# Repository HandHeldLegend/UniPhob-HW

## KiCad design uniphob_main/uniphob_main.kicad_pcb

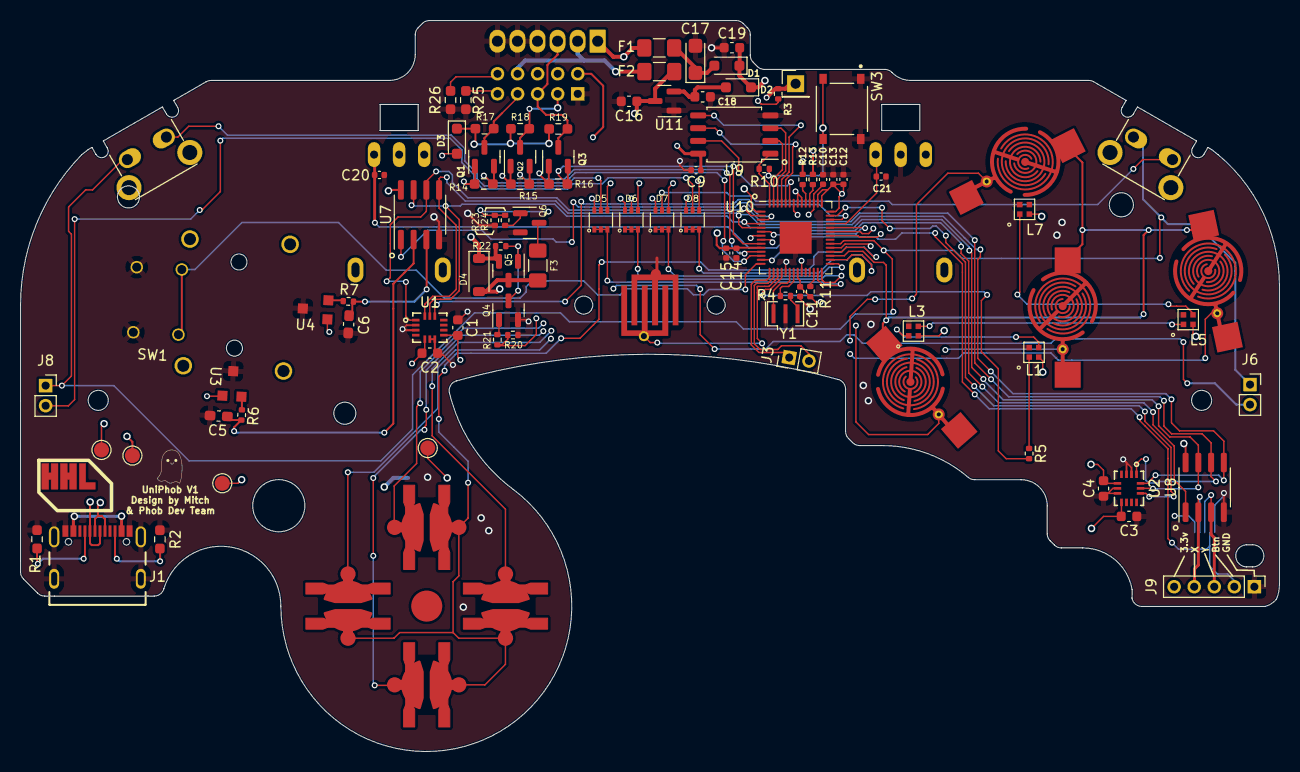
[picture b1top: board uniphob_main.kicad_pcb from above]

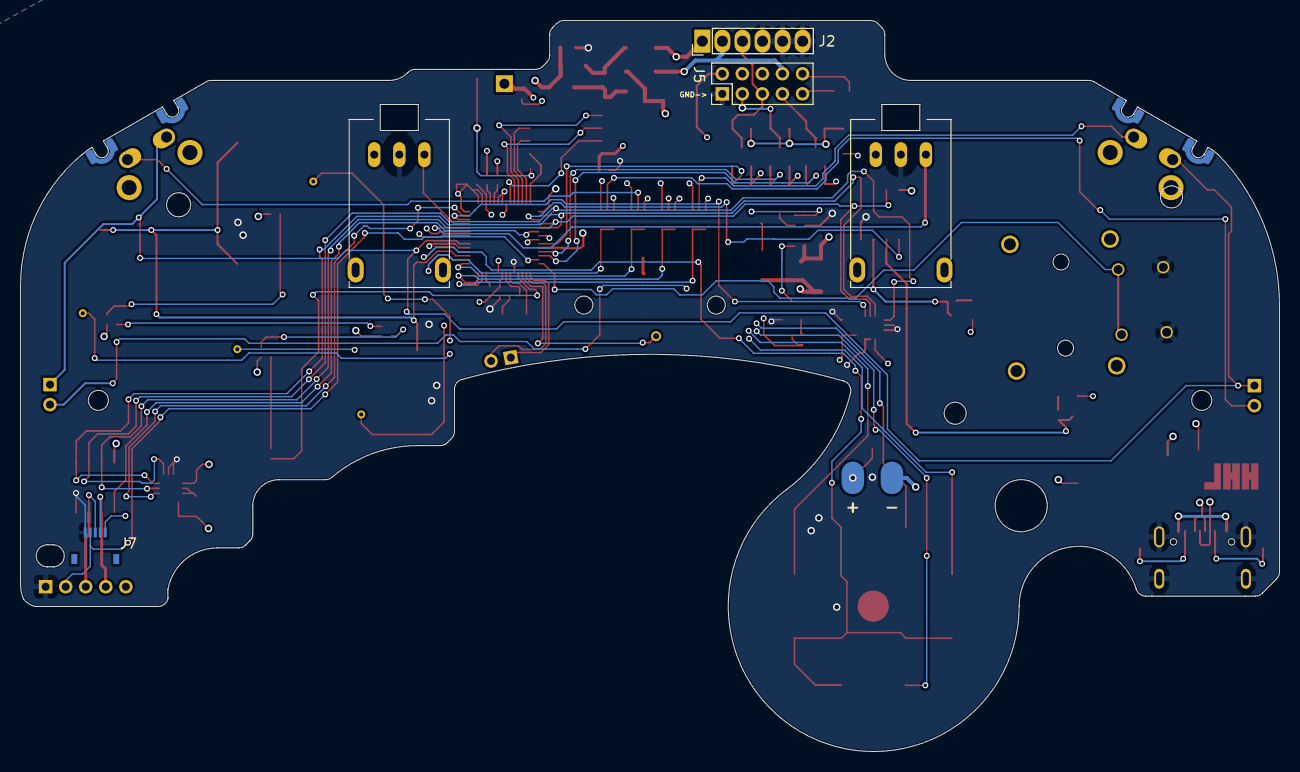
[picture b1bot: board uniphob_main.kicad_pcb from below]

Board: 4 copper layers, 125.5 x 72.9 mm, 103 parts (6 on the bottom side), 87 nets.

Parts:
C1, C2, C3, C4: 100nF; C_0603_1608Metric
C5, C6: .047u; C_0603_1608Metric_Pad1.08x0.95mm_HandSolder
C9, C10, C11, C12, C14, C15, C20, C21: 100n; C_0402_1005Metric
C13: 1u; C_0402_1005Metric
C16, C18: 2.2uF; C_0603_1608Metric
C17: 47uF 6.3v; CP_EIA-3216-18_Kemet-A
C19: 10u; C_0603_1608Metric
D1, D2, D3: CUS08F30; D_SOD-323_HandSoldering
D4: M7C; D_SOD-123
D5, D6, D7, D8: BAS16VY,115; SOT-363_SC-70-6
F1, F2, F3: Fuse; Fuse_1206_3216Metric_Pad1.42x1.75mm_HandSolder
J1: USB4105-GF-A-060; GCT_USB4105-GF-A-060
J2: Conn_01x06_Female; GCC_Header_Straight_1x06_Pitch2.00mm
J3: Conn_01x02_Pin; PinHeader_1x02_P2.00mm_Vertical
J4: Rumble; rumble_pins
J5: Conn_02x04_Counter_Clockwise; PinSocket_2x05_P2.00mm_Vertical
J6, J8: Conn_01x02_Socket; PinSocket_1x02_P2.00mm_Vertical
J7: Conn_01x05_Pin; molex_5034800540
J9: Conn_01x05_Pin; PinHeader_1x05_P2.00mm_Vertical
L1, L3, L5, L7: SK6805-EC-15
P1: Endpoint; PinHeader_1x01_P2.54mm_Vertical
Q1, Q2, Q3: BSS138; SOT-23
Q4, Q6: Q_NMOS_GSD; SOT-23
Q5: Q_PMOS_GDS; SOT-23
R1, R2, R25, R26: 5.1k; R_0603_1608Metric_Pad0.98x0.95mm_HandSolder
R3: 500K; R_0402_1005Metric
R4, R6, R7, R10: 1k; R_0402_1005Metric
R5: 330; R_0402_1005Metric
R11, R20, R22, R23: 10k; R_0402_1005Metric
R12, R13: 27; R_0402_1005Metric
R14, R15, R16, R17, R18, R19: 1k; R_0603_1608Metric_Pad0.98x0.95mm_HandSolder
R21, R24: 100R; R_0402_1005Metric
RV1, RV2: Slider_GCC-Gamecube_MB; GCC_Slider
SW1: GL18_SW; GL18
SW3: TS-1187A-B-A-B; SW_TS-1187A-B-A-B
SW4, SW5, SW6, SW7: BPAD; ABXY_Contact_Omron_Switch_Circley
SW8, SW9, SW10, SW11: DPAD; Dpad_Contact_TL3315NF_2_gba
SW12, SW14: BPAD; Z_Switch_Edge_Omron
SW16: BPAD; Start_Contact
TP1, TP2, TP5, TP7: TestPoint; TestPoint_Pad_D1.5mm
U1, U2: ST_LSM6; LGA14
U3, U4: GH39F (Hall SOT23); GH39F
U7, U8: MCP3002; SOIC-8_3.9x4.9mm_P1.27mm
U9: W25Q128JVS; SOIC-8_5.23x5.23mm_P1.27mm
U10: RP2040; QFN-56-1EP_7x7mm_P0.4mm_EP3.2x3.2mm
U11: LP3986-33B3F; SOT-23
Y1: Crystal_GND3; Resonator_SMD_Murata_CSTxExxV-3Pin_3.0x1.1mm

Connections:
+1V1: C10.2, U10.23 (DVDD), U10.45 (VREG_VOUT), U10.50 (DVDD)
+3.3V_PRE: F1.1, J2.1, J5.8
+3V3: C1.2, C2.2, C3.2, C4.2, C9.1, C11.1, C12.1, C13.1, C14.2, C15.2, C19.2, D1.1 (K), D2.1 (K), D3.2 (A), J7.5, J9.5, L1.2 (VDD), L3.2 (VDD), L5.2 (VDD), L7.2 (VDD), Q1.1 (G), Q2.1 (G), Q3.1 (G), R11.1, R14.1, R15.1, R16.1, RV1.1 (V+), RV2.1 (V+), TP7.1, U1.5 (VDDIO), U1.8 (VDD), U2.5 (VDDIO), U2.8 (VDD), U3.1 (VDD), U4.1 (VDD), U7.8 (VDD/VREF), U8.8 (VDD/VREF), U9.8 (VCC), U10.1 (IOVDD), U10.10 (IOVDD), U10.22 (IOVDD), U10.33 (IOVDD), U10.42 (IOVDD), U10.43 (ADC_AVDD), U10.44 (VREG_IN), U10.48 (USB_VDD), U10.49 (IOVDD)
+5V: C16.1, D4.1 (K), F2.2, J4.1, Q5.2 (S), R22.2, TP5.1, U11.3 (VI)
+5V_PRE: F2.1, J1.A4_B9 (VBUS), J1.B4_A9 (VBUS), J2.2, J5.7
/QSPI_SCLK: U9.6 (CLK), U10.52 (QSPI_SCLK)
/QSPI_SD0: U9.5 (DI(IO0)), U10.53 (QSPI_SD0)
/QSPI_SD1: U9.2 (DO(IO1)), U10.55 (QSPI_SD1)
/QSPI_SD2: U9.3 (IO2), U10.54 (QSPI_SD2)
/QSPI_SD3: U9.7 (IO3), U10.51 (QSPI_SD3)
/QSPI_SS: R10.1, U9.1 (~CS), U10.56 (QSPI_SS)
/RUN: R11.2, U10.26 (RUN)
/~USB_BOOT: R10.2, SW3.C, SW3.D
ABXY_RGB: L1.1 (DIN), R5.1
A_Pull: D7.6 (K), SW4.2
B_Pull: D8.6 (K), SW5.2
CC1: J5.5, R25.1
CC2: J5.6, R26.2
D+: J1.A6 (DP1), J1.B6 (DP2), J5.10, R12.1, TP2.1
D-: J1.A7 (DN1), J1.B7 (DN2), J5.9, R13.1, TP1.1
DD_Pull: D6.4 (K), SW9.2
DL_Pull: D8.4 (K), SW10.2
DR_Pull: D7.4 (K), SW11.2
DU_Pull: D5.4 (K), SW8.2
GND: C1.1, C2.1, C3.1, C4.1, C5.1, C6.1, C9.2, C10.1, C11.2, C12.2, C13.2, C14.1, C15.1, C16.2, C17.2, C18.2, C19.1, C20.2, C21.2, J1.A1_B12 (GND), J1.B1_A12 (GND), J1.S1 (SHELL_GND), J1.S2 (SHELL_GND), J1.S3 (SHELL_GND), J1.S4 (SHELL_GND), J2.4, J2.5, J2.6, J5.1, J7.1, J9.1, L1.4 (GND), L3.4 (GND), L5.4 (GND), L7.4 (GND), Q4.2 (S), Q6.2 (S), R1.2, R2.2, R20.1, R23.1, R25.2, R26.1, RV1.2 (GND), RV2.2 (GND), SW1.S3 (3), SW1.S4 (4), SW3.A, SW3.B, SW16.1, U1.2 (SDx), U1.3 (SCx), U1.6 (GNDIO), U1.7 (GND), U2.2 (SDx), U2.3 (SCx), U2.6 (GNDIO), U2.7 (GND), U3.3 (GND), U4.3 (GND), U7.4 (VSS), U8.4 (VSS), U9.4 (GND), U10.19 (TESTEN), U10.57 (GND), U11.1 (GND), Y1.2
IMU0_CS: U1.12 (CS), U10.40 (GPIO28_ADC2)
IMU1_CS: U2.12 (CS), U10.41 (GPIO29_ADC3)
LADC_CS: U7.1 (~CS/SHDN), U10.3 (GPIO1)
LS_BUTTON: SW1.S1 (1), SW1.S2 (2), U10.14 (GPIO11)
LX: C5.2, R6.2, U7.2 (CH0)
LY: C6.2, R7.2, U7.3 (CH1)
L_ANALOG: C20.1, RV1.3 (Signal), U10.38 (GPIO26_ADC0)
L_Pull: D8.5 (K), J8.2
N_CLOCK: J5.2, Q2.3 (D), R18.2
N_CLOCK_3.3: Q2.2 (S), R15.2, U10.11 (GPIO8)
N_DATA: J2.3, J5.3, Q3.3 (D), R19.2
N_DATA_3.3: Q3.2 (S), R16.2, U10.9 (GPIO7)
N_LATCH: J5.4, Q1.3 (D), R17.2
N_LATCH_3.3: Q1.2 (S), R14.2, U10.12 (GPIO9)
unnamed: C17.1, D1.2 (A), F1.2
unnamed: C18.1, D2.2 (A), U11.2 (VO)
unnamed: J1.A5 (CC1), R1.1
unnamed: J1.B5 (CC2), R2.1
unnamed: L1.3 (DOUT), L3.1 (DIN)
unnamed: L3.3 (DOUT), L5.1 (DIN)
unnamed: L5.3 (DOUT), L7.1 (DIN)
unnamed: Q4.3 (D), Q5.1 (G), R22.1
unnamed: Q4.1 (G), R21.2
unnamed: F3.2, Q6.3 (D)
unnamed: Q6.1 (G), R24.2
unnamed: R4.1, Y1.3
unnamed: R6.1, U3.2 (VOUT)
unnamed: R7.1, U4.2 (VOUT)
unnamed: R13.2, U10.46 (USB_DM)
unnamed: R12.2, U10.47 (USB_DP)
Push_A: D5.1 (A), D5.2 (A), D5.3 (A), U10.27 (GPIO16)
Push_B: D6.1 (A), D6.2 (A), D6.3 (A), U10.28 (GPIO17)
Push_C: D7.1 (A), D7.2 (A), D7.3 (A), U10.29 (GPIO18)
Push_D: D8.1 (A), D8.2 (A), D8.3 (A), U10.30 (GPIO19)
RADC_CS: U8.1 (~CS/SHDN), U10.6 (GPIO4)
RGB_OUT: R5.2, U10.18 (GPIO15)
RS_BUTTON: J7.2, J9.2, U10.13 (GPIO10)
RUMBLE: R23.2, R24.1, U10.37 (GPIO25)
RUMBLE-: D4.2 (A), F3.1, J4.2, Q5.3 (D)
RX: J7.4, J9.4, U8.2 (CH0)
RY: J7.3, J9.3, U8.3 (CH1)
R_ANALOG: C21.1, RV2.3 (Signal), U10.39 (GPIO27_ADC1)
R_BRAKE: R20.2, R21.1, U10.36 (GPIO24)
R_Pull: D6.5 (K), J6.2
SHARED_PU: D3.1 (K), R17.1, R18.1, R19.1
SPI_CK: U1.13 (SCL), U2.13 (SCL), U7.7 (CLK), U8.7 (CLK), U10.4 (GPIO2)
SPI_RX: U1.1 (SDO), U2.1 (SDO), U7.6 (DOUT), U8.6 (DOUT), U10.2 (GPIO0)
SPI_TX: U1.14 (SDA), U2.14 (SDA), U7.5 (DIN), U8.5 (DIN), U10.5 (GPIO3)
Scan_A: SW4.1, SW5.1, SW6.1, SW7.1, U10.31 (GPIO20)
Scan_B: SW8.1, SW9.1, SW10.1, SW11.1, U10.32 (GPIO21)
Scan_C: J6.1, J8.1, SW12.1, SW14.1, U10.34 (GPIO22)
Start_Button: SW16.2, U10.17 (GPIO14)
TOUCH_IN: R3.1, U10.7 (GPIO5)
TOUCH_OUT: P1.1, R3.2, U10.8 (GPIO6)
UART0_RX: J3.2, U10.16 (GPIO13)
UART0_TX: J3.1, U10.15 (GPIO12)
XTAL_IN: U10.20 (XIN), Y1.1
XTAL_OUT: R4.2, U10.21 (XOUT)
X_Pull: D5.6 (K), SW6.2
Y_Pull: D6.6 (K), SW7.2
ZL_Pull: D5.5 (K), SW12.2
ZR_Pull: D7.5 (K), SW14.2

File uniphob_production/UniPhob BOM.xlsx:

# | Reference | Qty | Value | Footprint | DNP | MPN
1.0 | C1, C2, C3, C4 | 4.0 | 100nF | Capacitor_SMD:C_0603_1608Metric
2.0 | C5, C6 | 2.0 | .047u | Capacitor_SMD:C_0603_1608Metric_Pad1.08x0.95mm_HandSolder
3.0 | C9, C10, C11, C12, C14, C15, C20, C21 | 8.0 | 100n | Capacitor_SMD:C_0402_1005Metric
4.0 | C13 | 1.0 | 1u | Capacitor_SMD:C_0402_1005Metric
5.0 | C16, C18 | 2.0 | 2.2uF | Capacitor_SMD:C_0603_1608Metric
6.0 | C17 | 1.0 | 47uF 6.3v | Capacitor_Tantalum_SMD:CP_EIA-3216-18_Kemet-A
7.0 | C19 | 1.0 | 10u | Capacitor_SMD:C_0603_1608Metric
8.0 | D1, D2, D3 | 3.0 | CUS08F30 | Diode_SMD:D_SOD-323_HandSoldering |  | CUS08F30
9.0 | D4 | 1.0 | M7C | Diode_SMD:D_SOD-123 |  | B5819W SL
10.0 | D5, D6, D7, D8 | 4.0 | BAS16VY,115 | uniphob_footprints:SOT-363_SC-70-6 |  | BAS16VY,115
11.0 | F1, F2, F3 | 3.0 | Fuse | Fuse:Fuse_1206_3216Metric_Pad1.42x1.75mm_HandSolder
12.0 | J1 | 1.0 | USB4105-GF-A-060 | uniphob_footprints:GCT_USB4105-GF-A-060 |  | USB4105-GF-A-060
13.0 | J5 | 1.0 | Conn_02x04_Counter_Clockwise | uniphob_footprints:PinSocket_2x05_P2.00mm_Vertical | CONSULT WITH DIAGRAM | ??
14.0 | J6, J8 | 2.0 | Conn_01x02_Socket | Connector_PinSocket_2.00mm:PinSocket_1x02_P2.00mm_Vertical | DNP
15.0 | J7 | 1.0 | Conn_01x05_Pin | uniphob_footprints:molex_5034800540 |  | molex_5034800540
16.0 | L1, L3, L5, L7 | 4.0 | SK6805-EC-15 | uniphob_footprints:SK6805-EC-15 |  | SK6805-EC-15
17.0 | Q1, Q2, Q3 | 3.0 | BSS138 | Package_TO_SOT_SMD:SOT-23 |  | BSS138
18.0 | Q4, Q6 | 2.0 | Q_NMOS_GSD | Package_TO_SOT_SMD:SOT-23 |  | AO3400A
19.0 | Q5 | 1.0 | Q_PMOS_GDS | Package_TO_SOT_SMD:SOT-23 |  | AO3401A
20.0 | R1, R2, R25, R26 | 4.0 | 5.1k | Resistor_SMD:R_0603_1608Metric_Pad0.98x0.95mm_HandSolder
21.0 | R3 | 1.0 | 500K | Resistor_SMD:R_0402_1005Metric
22.0 | R4, R6, R7, R10 | 4.0 | 1k | Resistor_SMD:R_0402_1005Metric
23.0 | R5 | 1.0 | 330.0 | Resistor_SMD:R_0402_1005Metric
24.0 | R11, R20, R22, R23 | 4.0 | 10k | Resistor_SMD:R_0402_1005Metric
25.0 | R12, R13 | 2.0 | 27.0 | Resistor_SMD:R_0402_1005Metric
26.0 | R14, R15, R16, R17, R18, R19 | 6.0 | 1k | Resistor_SMD:R_0603_1608Metric_Pad0.98x0.95mm_HandSolder
27.0 | R21, R24 | 2.0 | 100R | Resistor_SMD:R_0402_1005Metric
28.0 | RV1, RV2 | 2.0 | Slider_GCC-Gamecube_MB | uniphob_footprints:GCC_Slider |  | XP883
29.0 | SW1 | 1.0 | GL18_SW | uniphob_footprints:GL18 | DNP for prototype, I have extras | GL18
30.0 | SW3 | 1.0 | TS-1187A-B-A-B | uniphob_footprints:SW_TS-1187A-B-A-B |  | TS-1187A-B-A-B
31.0 | SW4, SW5, SW6, SW7 | 4.0 | BPAD | uniphob_footprints:ABXY_Contact_Omron_Switch_Circley | DNP
32.0 | SW12, SW14 | 2.0 | BPAD | uniphob_footprints:Z_Switch_Edge_Omron |  | TC-00100V
33.0 | SW16 | 1.0 | BPAD | uniphob_footprints:Start_Contact | DNP
34.0 | TP5, TP7 | 2.0 | TestPoint | TestPoint:TestPoint_Pad_D1.5mm | DNP
35.0 | U1, U2 | 2.0 | ST_LSM6 | uniphob_footprints:LGA14 |  | LSM6DSRTR
36.0 | U3, U4 | 2.0 | GH39F (Hall SOT23) | uniphob_footprints:GH39F |  | GH39F
37.0 | U7, U8 | 2.0 | MCP3002 | uniphob_footprints:SOIC-8_3.9x4.9mm_P1.27mm |  | MCP3002
38.0 | U9 | 1.0 | W25Q128JVS | Package_SO:SOIC-8_5.23x5.23mm_P1.27mm |  | W25Q128JVS
39.0 | U10 | 1.0 | RP2040 | Package_DFN_QFN:QFN-56-1EP_7x7mm_P0.4mm_EP3.2x3.2mm |  | RP2040
40.0 | U11 | 1.0 | LP3986-33B3F | Package_TO_SOT_SMD:SOT-23 |  | LP3986-33B3F
41.0 | Y1 | 1.0 | Crystal_GND3 | Crystal:Resonator_SMD_Murata_CSTxExxV-3Pin_3.0x1.1mm |  | CSTNE12M0GH5L000R0

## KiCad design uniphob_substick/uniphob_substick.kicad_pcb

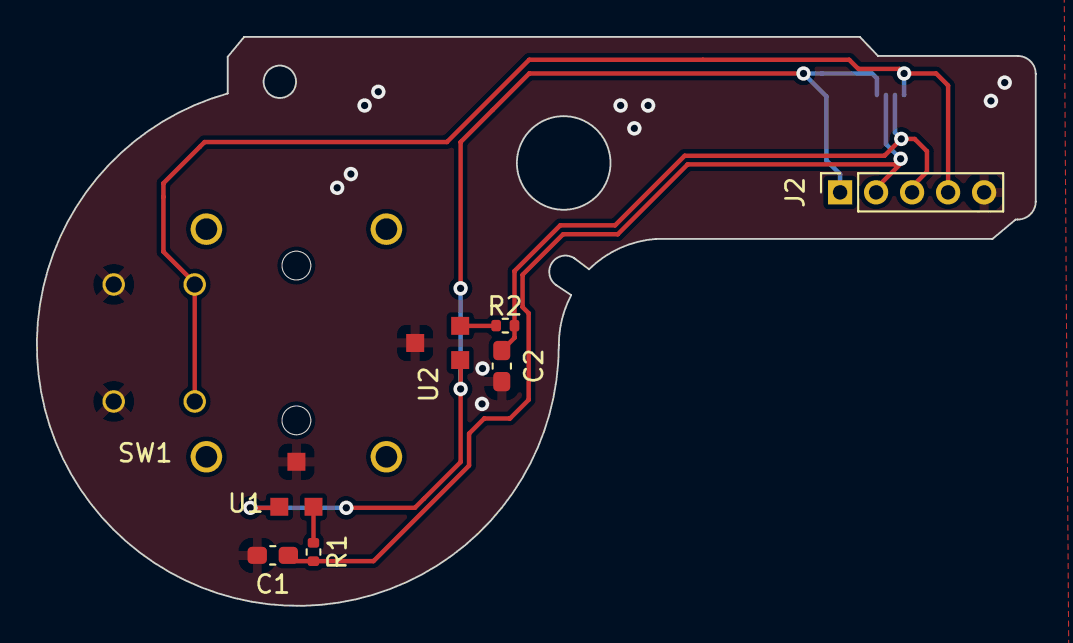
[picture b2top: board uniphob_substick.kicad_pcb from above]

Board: 2 copper layers, 55.5 x 31.6 mm, 9 parts (1 on the bottom side), 7 nets.

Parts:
C1, C2: .047u; C_0603_1608Metric_Pad1.08x0.95mm_HandSolder
J1: Conn_01x05_Pin; molex_5034800540
J2: Conn_01x05_Socket; PinSocket_1x05_P2.00mm_Vertical
R1, R2: 1k; R_0402_1005Metric
SW1: GL18_SW; GL18
U1, U2: GH39F (Hall SOT23); GH39F

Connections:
+3V3: J1.5, J2.1, U1.1 (VDD), U2.1 (VDD)
GND: C1.1, C2.1, J1.1, J2.5, SW1.S3 (3), SW1.S4 (4), U1.3 (GND), U2.3 (GND)
unnamed: R1.1, U1.2 (VOUT)
unnamed: R2.1, U2.2 (VOUT)
RS_BUTTON: J1.2, J2.4, SW1.S1 (1), SW1.S2 (2)
RX: C1.2, J1.4, J2.2, R1.2
RY: C2.2, J1.3, J2.3, R2.2

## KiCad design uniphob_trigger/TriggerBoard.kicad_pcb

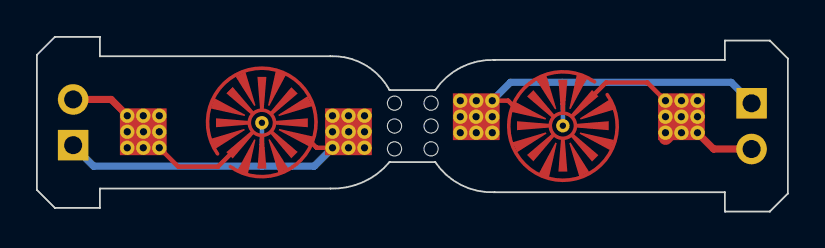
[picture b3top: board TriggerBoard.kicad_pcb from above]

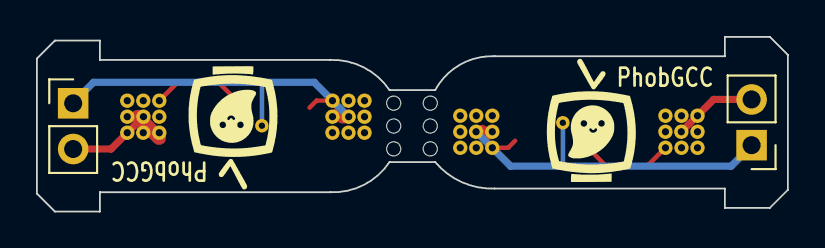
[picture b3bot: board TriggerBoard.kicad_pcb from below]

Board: 2 copper layers, 41.7 x 9.7 mm, 5 parts (2 on the bottom side), 4 nets.

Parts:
H2: MouseBiteRA; breakaway-mousebites-double
J1: L; Pin_Header_Straight_1x02_Pitch2.54mm
J2: R; Pin_Header_Straight_1x02_Pitch2.54mm
SW1: L; Trigger_Contact_Big
SW2: R; Trigger_Contact_Big

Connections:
unnamed: J1.1, SW1.1
unnamed: J1.2, SW1.2
unnamed: J2.1, SW2.1
unnamed: J2.2, SW2.2

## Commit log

2023-06-01 Schematic updates
2023-06-01 Checkpoint
2023-06-13 ROUTING
2023-06-14 Routing done
